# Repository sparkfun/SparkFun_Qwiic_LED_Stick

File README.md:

SparkFun Qwiic LED Stick
========================================

[*Qwiic LED Stick (COM-18354)*](https://www.sparkfun.com/products/18354)

The Qwiic LED Stick features ten addressable APA102 LEDs, making it easy to add full color LED control using I<sup>2</sup>C. Write to individual LEDs to display a count in binary, or write to the whole strip for cool lighting effects. We’ve written an Arduino library that takes care of the I<sup>2</sup>C and communication to the LEDs so all you have to do is decide what color each LED should be.

This board is one of our many [Qwiic](https://www.sparkfun.com/qwiic) compatible boards! Simply plug and go. No soldering, no figuring out which is SDA or SCL, and no voltage regulation or translation required!

SparkFun labored with love to create this code. Feel like supporting open source hardware? 
Buy a [board](https://www.sparkfun.com/products/18354) from SparkFun!

Repository Contents
-------------------

* **/Firmware** - Firmware
* **/Hardware** - Eagle design files (.brd, .sch)

Documentation
--------------
* **[Hookup Guide](https://learn.sparkfun.com/tutorials/qwiic-led-stick---apa102c-hookup-guide)** - A basic Hookup Guide to get started with the Qwiic LED Stick
* **[Qwiic LED Stick Arduino Library](https://github.com/sparkfun/SparkFun_Qwiic_LED_Stick_Arduino_Library)** - An Arduino library for Qwiic LED Stick
* **[Qwiic LED Stick Python Package]()** - A Python package for the Qwiic LED Stick.

Product Versions
----------------

* **[COM-18354](https://www.sparkfun.com/products/18354)** - Initial SparkFun release
* **[SPX-14783](https://www.sparkfun.com/products/14783)** - SparkX release

License Information
-------------------

This product is _**open source**_! 

If you have any questions or concerns on licensing, please contact techsupport@sparkfun.com.

Please use, reuse, and modify these files as you see fit. Please maintain attribution to SparkFun Electronics and release any derivative under the same license.

Distributed as-is; no warranty is given.

- Your friends at SparkFun.

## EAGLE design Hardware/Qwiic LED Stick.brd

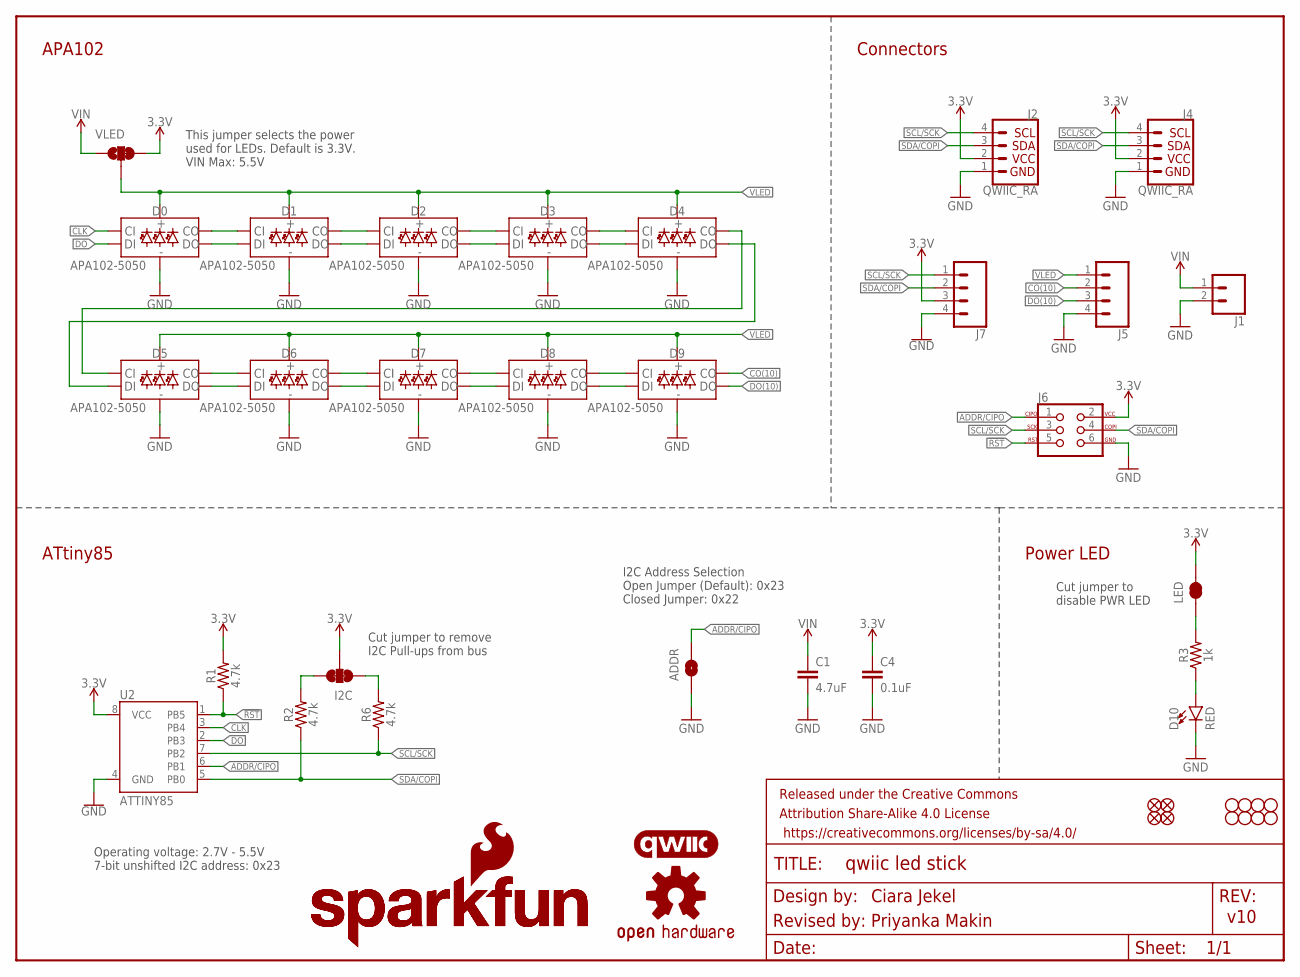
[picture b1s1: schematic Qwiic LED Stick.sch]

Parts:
ADDR: JUMPER-SMT_2_NO_SILK; SMT-JUMPER_2_NO_SILK
C1: 4.7uF; 0603
C4: 0.1uF; 0603
D0, D1, D2, D3, D4, D5, D6, D7, D8, D9: APA102-5050
D10: RED; LED-0603
FRAME1: FRAME-LETTER; CREATIVE_COMMONS
H1, H2, H3, H4: STAND-OFF
I2C: JUMPER-SMT_3_2-NC_TRACE_SILK; SMT-JUMPER_3_2-NC_TRACE_SILK
J1: CONN_021X02_NO_SILK; 1X02_NO_SILK
J2, J4: QWIIC_RA; JST04_1MM_RA
J5: CONN_041X04_NO_SILK; 1X04_NO_SILK
J6: AVR_SPI_PROG_3X2TESTPOINTS; 2X3_TEST_POINTS
J7: CONN_041X04_NO_SILK_NO_POP; 1X04_NO_SILK
JP1, JP2, JP5, JP6: FIDUCIALUFIDUCIAL; FIDUCIAL-MICRO
JP3, JP4, JP7, JP8: STAND-OFF
LED: JUMPER-SMT_2_NC_TRACE_SILK; SMT-JUMPER_2_NC_TRACE_SILK
LOGO1: OSHW-LOGOMINI; OSHW-LOGO-MINI
LOGO2, LOGO5: SFE_LOGO_NAME.2_INCH; SFE_LOGO_NAME_.2
LOGO3: QWIIC_LOGO_5MM; QWIIC_5MM
LOGO4: SFE_LOGO_FLAME.2_INCH; SFE_LOGO_FLAME_.2
R1, R2, R6: 4.7k; 0603
R3: 1k; 0603
U2: ATTINY85
VLED: JUMPER-SMT_3_1-NC_TRACE_SILK; SMT-JUMPER_3_1-NC_TRACE_SILK

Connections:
3.3V: C4.1, I2C.2, J2.2, J4.2, J6.2, J7.3, LED.2, R1.2, U2.8 (VCC), VLED.3
!RST: J6.5, R1.1, U2.1 (PB5)
ADDR/CIPO: ADDR.2, J6.1, U2.6 (PB1)
CLK: D0.P2 (CI), U2.3 (PB4)
CO(10): D9.P5 (CO), J5.2
DO: D0.P1 (DI), U2.2 (PB3)
DO(10): D9.P6 (DO), J5.3
GND: ADDR.1, C1.2, C4.2, D0.P3 (GND), D1.P3 (GND), D2.P3 (GND), D3.P3 (GND), D4.P3 (GND), D5.P3 (GND), D6.P3 (GND), D7.P3 (GND), D8.P3 (GND), D9.P3 (GND), D10.C, J1.2, J2.1, J4.1, J5.4, J6.6, J7.4, U2.4 (GND)
unnamed: D10.A, R3.1
unnamed: LED.1, R3.2
unnamed: I2C.3, R2.2
unnamed: I2C.1, R6.2
unnamed: D8.P6 (DO), D9.P1 (DI)
unnamed: D8.P5 (CO), D9.P2 (CI)
unnamed: D7.P5 (CO), D8.P2 (CI)
unnamed: D7.P6 (DO), D8.P1 (DI)
unnamed: D6.P5 (CO), D7.P2 (CI)
unnamed: D6.P6 (DO), D7.P1 (DI)
unnamed: D5.P5 (CO), D6.P2 (CI)
unnamed: D5.P6 (DO), D6.P1 (DI)
unnamed: D4.P5 (CO), D5.P2 (CI)
unnamed: D4.P6 (DO), D5.P1 (DI)
unnamed: D3.P5 (CO), D4.P2 (CI)
unnamed: D3.P6 (DO), D4.P1 (DI)
unnamed: D2.P6 (DO), D3.P1 (DI)
unnamed: D2.P5 (CO), D3.P2 (CI)
unnamed: D1.P6 (DO), D2.P1 (DI)
unnamed: D1.P5 (CO), D2.P2 (CI)
unnamed: D0.P5 (CO), D1.P2 (CI)
unnamed: D0.P6 (DO), D1.P1 (DI)
SCL/SCK: J2.4, J4.4, J6.3, J7.1, R6.1, U2.7 (PB2)
SDA/COPI: J2.3, J4.3, J6.4, J7.2, R2.1, U2.5 (PB0)
VIN: C1.1, J1.1, VLED.1
VLED: D0.P4 (VCC), D1.P4 (VCC), D2.P4 (VCC), D3.P4 (VCC), D4.P4 (VCC), D5.P4 (VCC), D6.P4 (VCC), D7.P4 (VCC), D8.P4 (VCC), D9.P4 (VCC), J5.1, VLED.2

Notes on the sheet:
v10
Cut jumper to remove I2C Pull-ups from bus
Cut jumper to disable PWR LED
Ciara Jekel
Operating voltage: 2.7V - 5.5V 7-bit unshifted I2C address: 0x23
I2C Address Selection Open Jumper (Default): 0x23 Closed Jumper: 0x22
This jumper selects the power used for LEDs. Default is 3.3V. VIN Max: 5.5V
Revised by: Priyanka Makin
APA102
Connectors
ATtiny85
Power LED

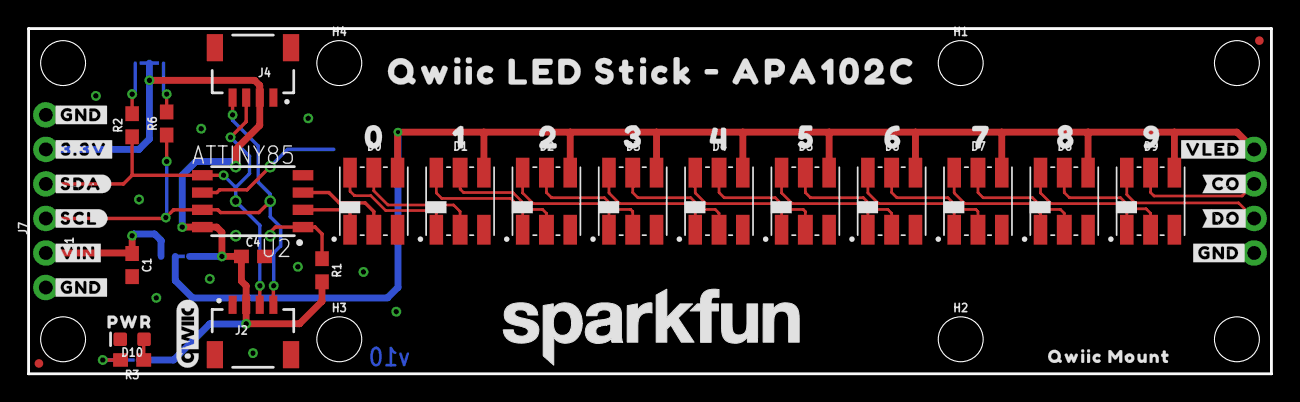
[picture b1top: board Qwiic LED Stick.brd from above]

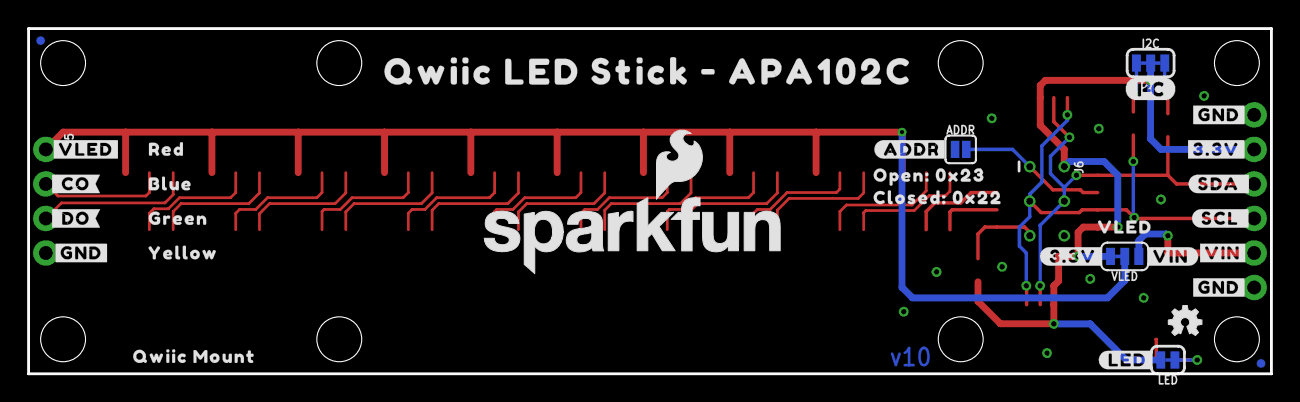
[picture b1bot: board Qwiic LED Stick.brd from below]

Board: 2 copper layers, 91.4 x 25.4 mm, 93 parts (35 on the bottom side), 34 nets.

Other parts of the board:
U$1, U$2, U$3, U$4, U$5, U$8: #GND#0
U$6: #CO#0
U$7: #DO#0
U$9, U$12: #VLED#0
U$10: #ADDR#0
U$11: (I_SUPER2_C)
U$14, U$17: #3#3V#0
U$15: #_DO#0
U$16: #_CO#0
U$18, U$19: #VIN#0
U$20: #SDA#0
U$21: #SDA_#0
U$22: #SCL#0
U$23: #SCL_#0
U$24: #LED#0
U$25: #3#3V#1
U$26: PWR0
U$28: VLED0
U$29: #VIN#4
U$30, U$47: QWIIC_MOUNT5
U$31: 00
U$32: 10
U$33: 20
U$34: 30
U$35: 40
U$36: 50
U$37: 60
U$38: 70
U$39: 80
U$40: 90
U$41: RED0
U$42: BLUE0
U$43: GREEN0
U$44: YELLOW0
U$45: OPEN#_0X230
U$46: CLOSED#_0X220
U$48, U$49: QWIIC_LED_STICK_#_APA102C0

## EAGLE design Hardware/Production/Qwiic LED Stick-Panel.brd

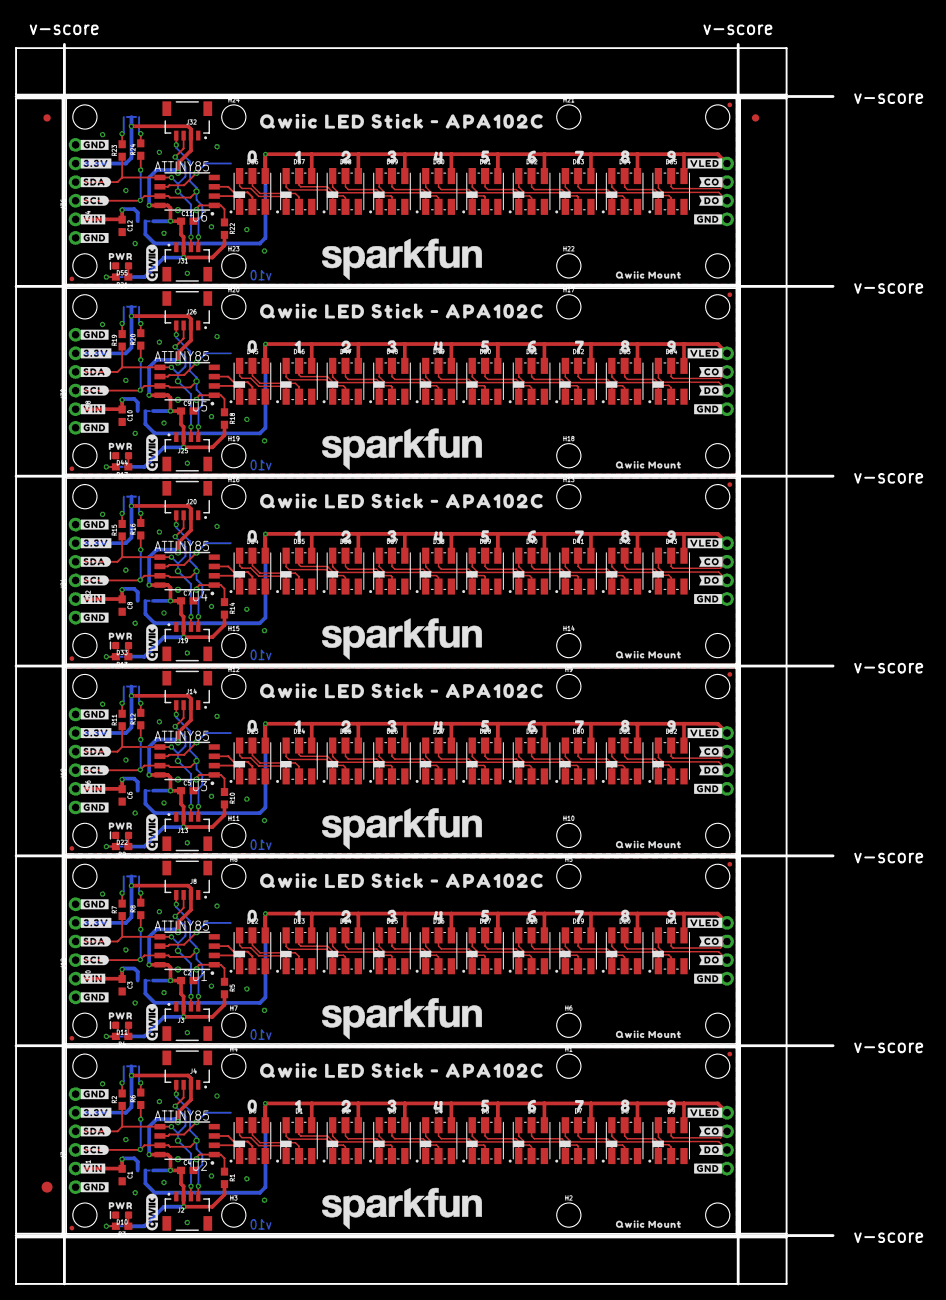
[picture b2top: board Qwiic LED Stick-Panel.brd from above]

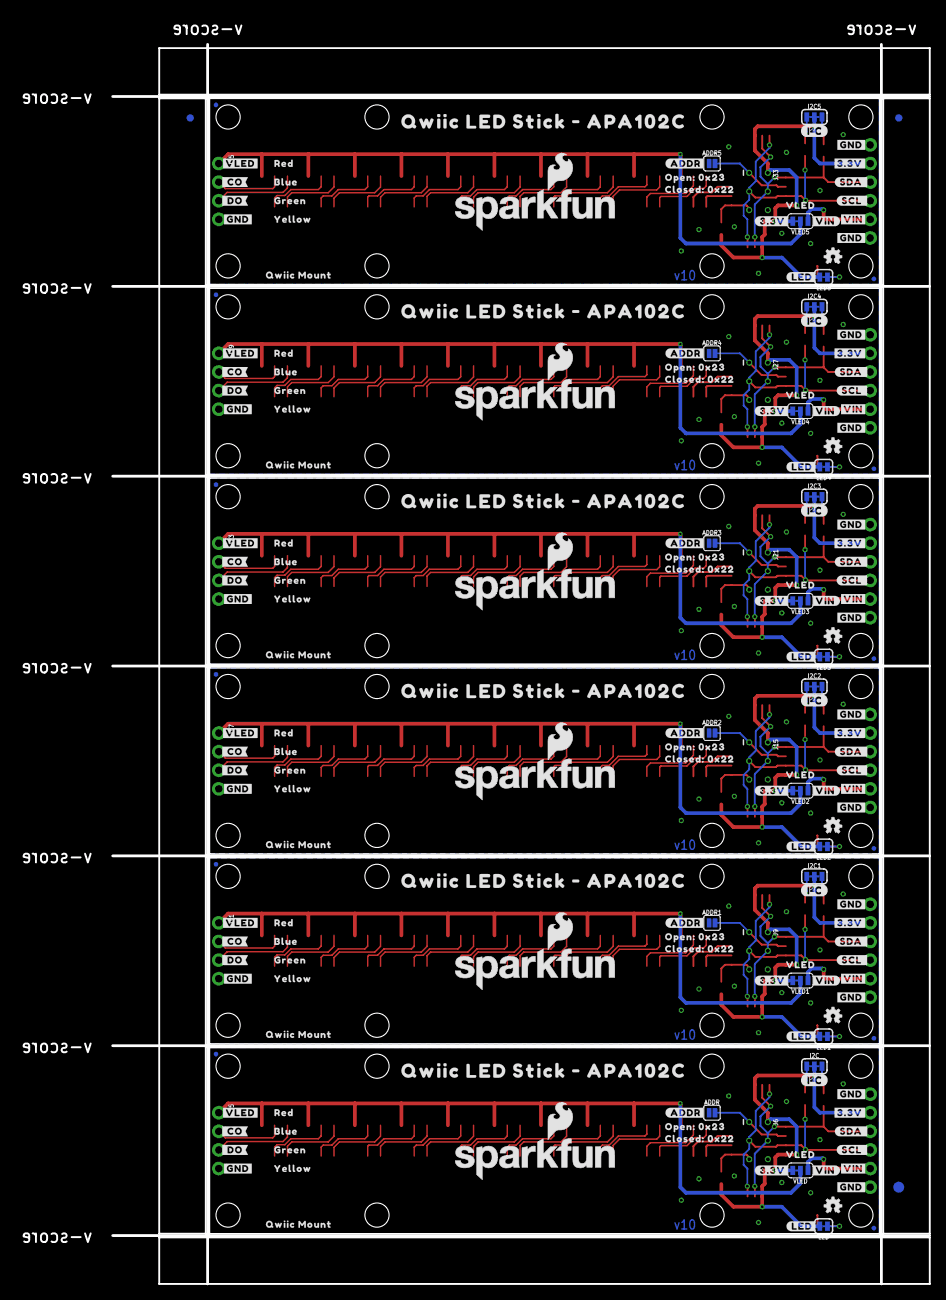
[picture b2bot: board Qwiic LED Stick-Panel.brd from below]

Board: 2 copper layers, 111.5 x 169.2 mm, 558 parts (213 on the bottom side), 204 nets.

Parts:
ADDR, ADDR1, ADDR2, ADDR3, ADDR4, ADDR5: JUMPER-SMT_2_NO_SILK; SMT-JUMPER_2_NO_SILK
C1, C3, C6, C8, C10, C12: 4.7uF; 0603
C2, C4, C5, C7, C9, C11: 0.1uF; 0603
D0, D1, D2, D3, D4, D5, D6, D7, D8, D9, D12, D13, D14, D15, D16, D17, D18, D19, D20, D21, D23, D24, D25, D26, D27, D28, D29, D30, D31, D32, D34, D35, D36, D37, D38, D39, D40, D41, D42, D43, D45, D46, D47, D48, D49, D50, D51, D52, D53, D54, D56, D57, D58, D59, D60, D61, D62, D63, D64, D65: APA102-5050
D10, D11, D22, D33, D44, D55: RED; LED-0603
E$1, E$2, E$3, E$4: FIDUCIAL-1X2
E$5, E$6: FIDUCIAL-1.5X3
H1, H2, H3, H4, H5, H6, H7, H8, H9, H10, H11, H12, H13, H14, H15, H16, H17, H18, H19, H20, H21, H22, H23, H24: STAND-OFF
I2C, I2C1, I2C2, I2C3, I2C4, I2C5: JUMPER-SMT_3_2-NC_TRACE_SILK; SMT-JUMPER_3_2-NC_TRACE_SILK
J1, J10, J16, J22, J28, J34: 1X02_NO_SILK
J2, J3, J4, J8, J13, J14, J19, J20, J25, J26, J31, J32: QWIIC_RA; JST04_1MM_RA
J5, J7, J11, J12, J17, J18, J23, J24, J29, J30, J35, J36: 1X04_NO_SILK
J6, J9, J15, J21, J27, J33: AVR_SPI_PROG_3X2TESTPOINTS; 2X3_TEST_POINTS
JP1, JP2, JP5, JP6, JP11, JP12, JP13, JP14, JP19, JP20, JP21, JP22, JP27, JP28, JP29, JP30, JP35, JP36, JP37, JP38, JP43, JP44, JP45, JP46: FIDUCIALUFIDUCIAL; FIDUCIAL-MICRO
JP3, JP4, JP7, JP8, JP9, JP10, JP15, JP16, JP17, JP18, JP23, JP24, JP25, JP26, JP31, JP32, JP33, JP34, JP39, JP40, JP41, JP42, JP47, JP48: STAND-OFF
LED, LED1, LED2, LED3, LED4, LED5: JUMPER-SMT_2_NC_TRACE_SILK; SMT-JUMPER_2_NC_TRACE_SILK
LOGO1, LOGO6, LOGO11, LOGO16, LOGO21, LOGO26: OSHW-LOGOMINI; OSHW-LOGO-MINI
LOGO2, LOGO5, LOGO7, LOGO10, LOGO12, LOGO15, LOGO17, LOGO20, LOGO22, LOGO25, LOGO27, LOGO30: SFE_LOGO_NAME.2_INCH; SFE_LOGO_NAME_.2
LOGO3, LOGO8, LOGO13, LOGO18, LOGO23, LOGO28: QWIIC_LOGO_5MM; QWIIC_5MM
LOGO4, LOGO9, LOGO14, LOGO19, LOGO24, LOGO29: SFE_LOGO_FLAME.2_INCH; SFE_LOGO_FLAME_.2
R1, R2, R5, R6, R7, R8, R10, R11, R12, R14, R15, R16, R18, R19, R20, R22, R23, R24: 4.7k; 0603
R3, R4, R9, R13, R17, R21: 1k; 0603
U1, U2, U3, U4, U5, U6: ATTINY85
U$1, U$2, U$3, U$4, U$5, U$8, U$27, U$50, U$51, U$52, U$62, U$63, U$96, U$97, U$98, U$99, U$109, U$110, U$143, U$144, U$145, U$146, U$156, U$157, U$190, U$191, U$192, U$193, U$203, U$204, U$237, U$238, U$239, U$240, U$250, U$251: #GND#0
U$6, U$66, U$113, U$160, U$207, U$254: #CO#0
U$7, U$67, U$114, U$161, U$208, U$255: #DO#0
U$9, U$12, U$64, U$65, U$111, U$112, U$158, U$159, U$205, U$206, U$252, U$253: #VLED#0
U$10, U$61, U$108, U$155, U$202, U$249: #ADDR#0
U$11, U$13, U$95, U$142, U$189, U$236: (I_SUPER2_C)
U$14, U$17, U$53, U$54, U$100, U$101, U$147, U$148, U$194, U$195, U$241, U$242: #3#3V#0
U$15, U$68, U$115, U$162, U$209, U$256: #_DO#0
U$16, U$69, U$116, U$163, U$210, U$257: #_CO#0
U$18, U$19, U$70, U$71, U$117, U$118, U$164, U$165, U$211, U$212, U$258, U$259: #VIN#0
U$20, U$55, U$102, U$149, U$196, U$243: #SDA#0
U$21, U$56, U$103, U$150, U$197, U$244: #SDA_#0
U$22, U$57, U$104, U$151, U$198, U$245: #SCL#0
U$23, U$58, U$105, U$152, U$199, U$246: #SCL_#0
U$24, U$59, U$106, U$153, U$200, U$247: #LED#0
U$25, U$73, U$120, U$167, U$214, U$261: #3#3V#1
U$26, U$60, U$107, U$154, U$201, U$248: PWR0
U$28, U$72, U$119, U$166, U$213, U$260: VLED0
U$29, U$74, U$121, U$168, U$215, U$262: #VIN#4
U$30, U$47, U$75, U$92, U$122, U$139, U$169, U$186, U$216, U$233, U$263, U$280: QWIIC_MOUNT5
U$31, U$76, U$123, U$170, U$217, U$264: 00
U$32, U$77, U$124, U$171, U$218, U$265: 10
U$33, U$78, U$125, U$172, U$219, U$266: 20
U$34, U$79, U$126, U$173, U$220, U$267: 30
U$35, U$80, U$127, U$174, U$221, U$268: 40
U$36, U$81, U$128, U$175, U$222, U$269: 50
U$37, U$82, U$129, U$176, U$223, U$270: 60
U$38, U$83, U$130, U$177, U$224, U$271: 70
U$39, U$84, U$131, U$178, U$225, U$272: 80
U$40, U$85, U$132, U$179, U$226, U$273: 90
U$41, U$86, U$133, U$180, U$227, U$274: RED0
U$42, U$87, U$134, U$181, U$228, U$275: BLUE0
U$43, U$88, U$135, U$182, U$229, U$276: GREEN0
U$44, U$89, U$136, U$183, U$230, U$277: YELLOW0
U$45, U$90, U$137, U$184, U$231, U$278: OPEN#_0X230
U$46, U$91, U$138, U$185, U$232, U$279: CLOSED#_0X220
U$48, U$49, U$93, U$94, U$140, U$141, U$187, U$188, U$234, U$235, U$281, U$282: QWIIC_LED_STICK_#_APA102C0
VLED, VLED1, VLED2, VLED3, VLED4, VLED5: JUMPER-SMT_3_1-NC_TRACE_SILK; SMT-JUMPER_3_1-NC_TRACE_SILK

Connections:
3.3V: C4.1, I2C.2, J2.2, J4.2, J6.2, J7.3, LED.2, R1.2, U2.8, VLED.3
3.3V1: C2.1, I2C1.2, J3.2, J8.2, J9.2, J12.3, LED1.2, R5.2, U1.8, VLED1.3
3.3V2: C5.1, I2C2.2, J13.2, J14.2, J15.2, J18.3, LED2.2, R10.2, U3.8, VLED2.3
3.3V3: C7.1, I2C3.2, J19.2, J20.2, J21.2, J24.3, LED3.2, R14.2, U4.8, VLED3.3
3.3V4: C9.1, I2C4.2, J25.2, J26.2, J27.2, J30.3, LED4.2, R18.2, U5.8, VLED4.3
3.3V5: C11.1, I2C5.2, J31.2, J32.2, J33.2, J36.3, LED5.2, R22.2, U6.8, VLED5.3
!RST: J6.5, R1.1, U2.1
!RST1: J9.5, R5.1, U1.1
!RST2: J15.5, R10.1, U3.1
!RST3: J21.5, R14.1, U4.1
!RST4: J27.5, R18.1, U5.1
!RST5: J33.5, R22.1, U6.1
ADDR/CIPO: ADDR.2, J6.1, U2.6
ADDR/CIPO1: ADDR1.2, J9.1, U1.6
ADDR/CIPO2: ADDR2.2, J15.1, U3.6
ADDR/CIPO3: ADDR3.2, J21.1, U4.6
ADDR/CIPO4: ADDR4.2, J27.1, U5.6
ADDR/CIPO5: ADDR5.2, J33.1, U6.6
CLK: D0.P2, U2.3
CLK1: D12.P2, U1.3
CLK2: D23.P2, U3.3
CLK3: D34.P2, U4.3
CLK4: D45.P2, U5.3
CLK5: D56.P2, U6.3
CO(10): D9.P5, J5.2
CO(10)1: D21.P5, J11.2
CO(10)2: D32.P5, J17.2
CO(10)3: D43.P5, J23.2
CO(10)4: D54.P5, J29.2
CO(10)5: D65.P5, J35.2
DO: D0.P1, U2.2
DO1: D12.P1, U1.2
DO2: D23.P1, U3.2
DO3: D34.P1, U4.2
DO4: D45.P1, U5.2
DO5: D56.P1, U6.2
DO(10): D9.P6, J5.3
DO(10)1: D21.P6, J11.3
DO(10)2: D32.P6, J17.3
DO(10)3: D43.P6, J23.3
DO(10)4: D54.P6, J29.3
DO(10)5: D65.P6, J35.3
GND: ADDR.1, C1.2, C4.2, D0.P3, D1.P3, D2.P3, D3.P3, D4.P3, D5.P3, D6.P3, D7.P3, D8.P3, D9.P3, D10.C, J1.2, J2.1, J4.1, J5.4, J6.6, J7.4, U2.4
GND1: ADDR1.1, C2.2, C3.2, D11.C, D12.P3, D13.P3, D14.P3, D15.P3, D16.P3, D17.P3, D18.P3, D19.P3, D20.P3, D21.P3, J3.1, J8.1, J9.6, J10.2, J11.4, J12.4, U1.4
GND2: ADDR2.1, C5.2, C6.2, D22.C, D23.P3, D24.P3, D25.P3, D26.P3, D27.P3, D28.P3, D29.P3, D30.P3, D31.P3, D32.P3, J13.1, J14.1, J15.6, J16.2, J17.4, J18.4, U3.4
GND3: ADDR3.1, C7.2, C8.2, D33.C, D34.P3, D35.P3, D36.P3, D37.P3, D38.P3, D39.P3, D40.P3, D41.P3, D42.P3, D43.P3, J19.1, J20.1, J21.6, J22.2, J23.4, J24.4, U4.4
GND4: ADDR4.1, C9.2, C10.2, D44.C, D45.P3, D46.P3, D47.P3, D48.P3, D49.P3, D50.P3, D51.P3, D52.P3, D53.P3, D54.P3, J25.1, J26.1, J27.6, J28.2, J29.4, J30.4, U5.4
GND5: ADDR5.1, C11.2, C12.2, D55.C, D56.P3, D57.P3, D58.P3, D59.P3, D60.P3, D61.P3, D62.P3, D63.P3, D64.P3, D65.P3, J31.1, J32.1, J33.6, J34.2, J35.4, J36.4, U6.4
unnamed: D11.A, R4.1
unnamed: D20.P6, D21.P1
unnamed: D10.A, R3.1
unnamed: LED.1, R3.2
unnamed: I2C.3, R2.2
unnamed: I2C.1, R6.2
unnamed: D20.P5, D21.P2
unnamed: D8.P6, D9.P1
unnamed: D8.P5, D9.P2
unnamed: D7.P5, D8.P2
unnamed: D7.P6, D8.P1
unnamed: D6.P5, D7.P2
unnamed: D6.P6, D7.P1
unnamed: D5.P5, D6.P2
unnamed: D5.P6, D6.P1
unnamed: D4.P5, D5.P2
unnamed: D4.P6, D5.P1
unnamed: D3.P5, D4.P2
unnamed: D3.P6, D4.P1
unnamed: D2.P6, D3.P1
unnamed: D2.P5, D3.P2
unnamed: D1.P6, D2.P1
unnamed: D1.P5, D2.P2
unnamed: D0.P5, D1.P2
unnamed: D0.P6, D1.P1
unnamed: D19.P5, D20.P2
unnamed: D19.P6, D20.P1
unnamed: D18.P5, D19.P2
unnamed: D18.P6, D19.P1
unnamed: D17.P5, D18.P2
unnamed: D17.P6, D18.P1
unnamed: D16.P5, D17.P2
unnamed: D16.P6, D17.P1
unnamed: D15.P5, D16.P2
unnamed: D15.P6, D16.P1
unnamed: D14.P6, D15.P1
unnamed: D14.P5, D15.P2
unnamed: D13.P6, D14.P1
unnamed: D13.P5, D14.P2
unnamed: D12.P5, D13.P2
unnamed: D12.P6, D13.P1
unnamed: LED1.1, R4.2
unnamed: I2C1.3, R7.2
unnamed: I2C1.1, R8.2
unnamed: D22.A, R9.1
unnamed: D31.P6, D32.P1
unnamed: D31.P5, D32.P2
unnamed: D30.P5, D31.P2
unnamed: D30.P6, D31.P1
unnamed: D29.P5, D30.P2
unnamed: D29.P6, D30.P1
unnamed: D28.P5, D29.P2
unnamed: D28.P6, D29.P1
unnamed: D27.P5, D28.P2
unnamed: D27.P6, D28.P1
unnamed: D26.P5, D27.P2
unnamed: D26.P6, D27.P1
unnamed: D25.P6, D26.P1
unnamed: D25.P5, D26.P2
unnamed: D24.P6, D25.P1
unnamed: D24.P5, D25.P2
unnamed: D23.P5, D24.P2
unnamed: D23.P6, D24.P1
unnamed: LED2.1, R9.2
unnamed: I2C2.3, R11.2
unnamed: I2C2.1, R12.2
unnamed: D33.A, R13.1
unnamed: D42.P6, D43.P1
unnamed: D42.P5, D43.P2
unnamed: D41.P5, D42.P2
unnamed: D41.P6, D42.P1
unnamed: D40.P5, D41.P2
unnamed: D40.P6, D41.P1
unnamed: D39.P5, D40.P2
unnamed: D39.P6, D40.P1
unnamed: D38.P5, D39.P2
unnamed: D38.P6, D39.P1
unnamed: D37.P5, D38.P2
unnamed: D37.P6, D38.P1
unnamed: D36.P6, D37.P1
unnamed: D36.P5, D37.P2
unnamed: D35.P6, D36.P1
unnamed: D35.P5, D36.P2
unnamed: D34.P5, D35.P2
unnamed: D34.P6, D35.P1
unnamed: LED3.1, R13.2
unnamed: I2C3.3, R15.2
unnamed: I2C3.1, R16.2
unnamed: D44.A, R17.1
unnamed: D53.P6, D54.P1
unnamed: D53.P5, D54.P2
unnamed: D52.P5, D53.P2
unnamed: D52.P6, D53.P1
unnamed: D51.P5, D52.P2
unnamed: D51.P6, D52.P1
unnamed: D50.P5, D51.P2
unnamed: D50.P6, D51.P1
unnamed: D49.P5, D50.P2
unnamed: D49.P6, D50.P1
unnamed: D48.P5, D49.P2
unnamed: D48.P6, D49.P1
unnamed: D47.P6, D48.P1
unnamed: D47.P5, D48.P2
unnamed: D46.P6, D47.P1
unnamed: D46.P5, D47.P2
unnamed: D45.P5, D46.P2
unnamed: D45.P6, D46.P1
unnamed: LED4.1, R17.2
unnamed: I2C4.3, R19.2
unnamed: I2C4.1, R20.2
unnamed: D55.A, R21.1
unnamed: D64.P6, D65.P1
unnamed: D64.P5, D65.P2
unnamed: D63.P5, D64.P2
unnamed: D63.P6, D64.P1
unnamed: D62.P5, D63.P2
unnamed: D62.P6, D63.P1
unnamed: D61.P5, D62.P2
unnamed: D61.P6, D62.P1
unnamed: D60.P5, D61.P2
unnamed: D60.P6, D61.P1
unnamed: D59.P5, D60.P2
unnamed: D59.P6, D60.P1
unnamed: D58.P6, D59.P1
unnamed: D58.P5, D59.P2
unnamed: D57.P6, D58.P1
unnamed: D57.P5, D58.P2
unnamed: D56.P5, D57.P2
unnamed: D56.P6, D57.P1
unnamed: LED5.1, R21.2
unnamed: I2C5.3, R23.2
unnamed: I2C5.1, R24.2
SCL/SCK: J2.4, J4.4, J6.3, J7.1, R6.1, U2.7
SCL/SCK1: J3.4, J8.4, J9.3, J12.1, R8.1, U1.7
SCL/SCK2: J13.4, J14.4, J15.3, J18.1, R12.1, U3.7
SCL/SCK3: J19.4, J20.4, J21.3, J24.1, R16.1, U4.7
SCL/SCK4: J25.4, J26.4, J27.3, J30.1, R20.1, U5.7
SCL/SCK5: J31.4, J32.4, J33.3, J36.1, R24.1, U6.7
SDA/COPI: J2.3, J4.3, J6.4, J7.2, R2.1, U2.5
SDA/COPI1: J3.3, J8.3, J9.4, J12.2, R7.1, U1.5
SDA/COPI2: J13.3, J14.3, J15.4, J18.2, R11.1, U3.5
SDA/COPI3: J19.3, J20.3, J21.4, J24.2, R15.1, U4.5
SDA/COPI4: J25.3, J26.3, J27.4, J30.2, R19.1, U5.5
SDA/COPI5: J31.3, J32.3, J33.4, J36.2, R23.1, U6.5
VIN: C1.1, J1.1, VLED.1
VIN1: C3.1, J10.1, VLED1.1
VIN2: C6.1, J16.1, VLED2.1
VIN3: C8.1, J22.1, VLED3.1
VIN4: C10.1, J28.1, VLED4.1
VIN5: C12.1, J34.1, VLED5.1
VLED: D0.P4, D1.P4, D2.P4, D3.P4, D4.P4, D5.P4, D6.P4, D7.P4, D8.P4, D9.P4, J5.1, VLED.2
VLED1: D12.P4, D13.P4, D14.P4, D15.P4, D16.P4, D17.P4, D18.P4, D19.P4, D20.P4, D21.P4, J11.1, VLED1.2
VLED2: D23.P4, D24.P4, D25.P4, D26.P4, D27.P4, D28.P4, D29.P4, D30.P4, D31.P4, D32.P4, J17.1, VLED2.2
VLED3: D34.P4, D35.P4, D36.P4, D37.P4, D38.P4, D39.P4, D40.P4, D41.P4, D42.P4, D43.P4, J23.1, VLED3.2
VLED4: D45.P4, D46.P4, D47.P4, D48.P4, D49.P4, D50.P4, D51.P4, D52.P4, D53.P4, D54.P4, J29.1, VLED4.2
VLED5: D56.P4, D57.P4, D58.P4, D59.P4, D60.P4, D61.P4, D62.P4, D63.P4, D64.P4, D65.P4, J35.1, VLED5.2

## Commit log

2021-06-01 Update schematic and board for transition
    Brought schematic and board routing up to current standards
2021-06-01 Update logos
2021-06-01 New buzzard labels
2021-06-02 Design review changes:
    Sch:
    Re-number diodes starting at 0
    Change VCC net label to VIN
    Added 4 more stand off holes for 1x1 qwiic
    Board:
    Added measures for PTH and LEDs
2021-06-02 Update silk screen
2021-06-02 Checklist
2021-06-03 Panelize
2021-06-04 Update comments on sch
2021-06-04 Increase buzzard labels
2021-06-04 Re-panelize
2021-06-30 Update firmware to fix LED indexing
    Single LED indexing now starts at 0 like indicated on the PCB silkscreen.
    Also replaced datasheet with the correct one for these LEDs
2021-07-07 Update to firmware, new binaries generated
2021-07-13 Update README.md
    Updating README.md for product release.

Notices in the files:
parts and their libraries:
SparkFun-Resistors: Licensing: Creative Commons ShareAlike 4.0 International - https://creativecommons.org/licenses/by-sa/4.0
SparkFun-Aesthetics: Released under the Creative Commons Attribution Share-Alike 4.0 License
SparkFun-Aesthetics: https://creativecommons.org/licenses/by-sa/4.0
